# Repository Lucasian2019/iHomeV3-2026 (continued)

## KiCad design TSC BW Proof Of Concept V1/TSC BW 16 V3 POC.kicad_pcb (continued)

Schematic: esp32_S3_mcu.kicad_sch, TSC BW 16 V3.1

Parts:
C7: 0.1uF; C_1206_3216Metric
C8: 22uF; C_1206_3216Metric
J3: Free GPIO !pull-up; PhoenixContact_MSTBA_2,5_3-G-5,08_1x03_P5.08mm_Horizontal
J4: Free GPIO pull-up; PhoenixContact_MSTBA_2,5_3-G-5,08_1x03_P5.08mm_Horizontal
J19: 691312510002; PhoenixContact_MSTBA_2,5_2-G-5,08_1x02_P5.08mm_Horizontal
R5, R6: 4.7k; R_1206_3216Metric_Pad1.30x1.75mm_HandSolder
R7, R8, R9: 10k; R_1206_3216Metric_Pad1.30x1.75mm_HandSolder
U3: ESP32-S3-WROOM-1

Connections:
485RX: U3.10 (IO17); also elsewhere on the board
485TX: U3.9 (IO16); also elsewhere on the board
485_EN: U3.23 (IO21); also elsewhere on the board
+3V3: C7.2, C8.2, R5.1, R6.1, R7.2, R8.2, R9.2, U3.2 (3V3); also elsewhere on the board
/ESP32 S3 MCU/F_IO38: J4.1, R7.1, U3.31 (IO38)
/ESP32 S3 MCU/F_IO39: J3.1, U3.32 (IO39)
/ESP32 S3 MCU/F_IO40: J3.2, U3.33 (IO40)
/ESP32 S3 MCU/F_IO41: J3.3, U3.34 (IO41)
/ESP32 S3 MCU/F_IO47: J4.2, R8.1, U3.24 (IO47)
/ESP32 S3 MCU/F_IO48: J4.3, R9.1
ANALOG_A1: U3.4 (IO4); also elsewhere on the board
ANALOG_A2: U3.6 (IO6); also elsewhere on the board
ANALOG_A3: U3.7 (IO7); also elsewhere on the board
ANALOG_A4: U3.5 (IO5); also elsewhere on the board
BUZZER: U3.25 (IO48); also elsewhere on the board
EN: U3.3 (EN); also elsewhere on the board
ETH_INT: U3.38 (IO2); also elsewhere on the board
ETH_MISO: U3.14 (USB_D+); also elsewhere on the board
ETH_MOSI: U3.13 (USB_D-); also elsewhere on the board
ETH_RST: U3.39 (IO1); also elsewhere on the board
ETH_SCLK: U3.35 (IO42); also elsewhere on the board
ETH_SCS: U3.8 (IO15); also elsewhere on the board
GND: C7.1, C8.1, U3.1 (GND), U3.40 (GND), U3.41 (GND); also elsewhere on the board
IO0: U3.27 (IO0); also elsewhere on the board
RXD: U3.36 (RXD0); also elsewhere on the board
SCL: J19.1, R6.2, U3.18 (IO10); also elsewhere on the board
SDA: J19.2, R5.2, U3.17 (IO9); also elsewhere on the board
SD_CLK: U3.21 (IO13)
SD_CS: U3.19 (IO11); also elsewhere on the board
SD_MISO: U3.22 (IO14)
SD_MOSI: U3.20 (IO12); also elsewhere on the board
TXD: U3.37 (TXD0); also elsewhere on the board

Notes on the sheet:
free GPIOs with pull-up: f-io-1:GPIO39 f-io-2:GPIO40 f-io-3:GPIO41
BUZZER - PIN25 : GPIO48
Pull-Up Resistors
SD CARD GLOBAL PINS / LABELS P7
BUZZER GLOBAL PINS / LABELS P13
RS485 TXD - PIN9 : GPIO16 RXD - PIN10 : GPIO17 TXD - PIN23 : GPIO21
1 RTC P6
SDA - PIN17 : GPIO9 SCL - PIN18 : GPIO10
3 DIGITAL OUTPUT P5
Ethernet (W5500) ETH_SCLK - PIN35 : GPIO42 ETH_MOSI - PIN37 : GPIO43 ETH_MISO - PIN36 : GPIO44 ETH_SCS - PIN8 : GPIO15 ETH_INT - PIN38 : GPIO2 ETH_RST - PIN39 : GPIO1
USB C - UART EN- PIN3 : NO GPIO IO0 - PIN27 : GPIO0 RXD - PIN36/RXD0 : GPIO44,U0RXD TXD - PIN37/ TXD0 : GPIO43,U0TXD
i2c sda: 9 scl: 10
SD Card (SPI) MOSI - PIN20 : GPIO12 SCK - PIN21 : GPIO13 MISO - PIN22 : GPIO14 CS - PIN19 : GPIO11 SD-CD - PIN23 : GPIO21
2 DIGITAL INPUT P4
FREE GPIO with pull-up on PCB 1 - PIN31 : GPIO38 2 - PIN24 : GPIO47 3 - PIN25 : GPIO48
ETHERNET GLOBAL PINS / LABELS P15
Analog Inputs ANALOG_A1 - PIN4 : GPIO4 ANALOG_A2 - PIN6 : GPIO6 ANALOG_A3 - PIN7 : GPIO7 ANALOG_A4 - PIN5 : GPIO5
I2C PULL UPS
I2C GLOBAL PINS / LABELS
USB C - UART GLOBAL PINS / LABELS P11
ADC PINS / LABELS P14
RS485 V2 GLOBAL PINS / LABELS P10
free GPIOs without pull-up: f-io-1:GPIO39 f-io-2:GPIO40 f-io-3:GPIO41
Free GPIOs (without pull-up on PCB) 1 - PIN32 : GPIO39 2 - PIN33 : GPIO40 3 - PIN34 : GPIO41

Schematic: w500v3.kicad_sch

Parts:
C47, C48: 12pF; C_0603_1608Metric_Pad1.08x0.95mm_HandSolder
C49, C50, C51, C52, C53, C54, C64: 100nF; C_0603_1608Metric_Pad1.08x0.95mm_HandSolder
C55, C59: 10nF; C_0603_1608Metric_Pad1.08x0.95mm_HandSolder
C56: 4.7uF/6.3V; C_0603_1608Metric_Pad1.08x0.95mm_HandSolder
C57: 22nF; C_0603_1608Metric_Pad1.08x0.95mm_HandSolder
C61: 102/1KV; C_0603_1608Metric_Pad1.08x0.95mm_HandSolder
C62, C63: 10uF/10v; C_0603_1608Metric_Pad1.08x0.95mm_HandSolder
C65, C66: 6.8nF; C_0603_1608Metric_Pad1.08x0.95mm_HandSolder
J18: RJ45_Hanrun_HR911105A_Horizontal
JP5: SolderJumper_2_Open; SolderJumper-2_P1.3mm_Open_RoundedPad1.0x1.5mm
R183, R186: 10K; R_0603_1608Metric_Pad0.98x0.95mm_HandSolder
R184: 10K; R_0603_1608Metric
R188: 12.4k 1%; R_0603_1608Metric_Pad0.98x0.95mm_HandSolder
R189, R190: 49R9; R_0603_1608Metric_Pad0.98x0.95mm_HandSolder
R191: 10R; R_0603_1608Metric_Pad0.98x0.95mm_HandSolder
R192, R193: 82R; R_0603_1608Metric_Pad0.98x0.95mm_HandSolder
R194: 1M; R_0603_1608Metric_Pad0.98x0.95mm_HandSolder
R197, R198: 1k; R_0603_1608Metric_Pad0.98x0.95mm_HandSolder
RN3: R_Pack04; R_Array_Convex_4x0603
RN10: 10K R_Pack05; R_Array_Convex_5x0603
U46: W5500; LQFP-48_7x7mm_P0.5mm
Y4: 25M; Crystal_SMD_3225-4Pin_3.2x2.5mm

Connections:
+3V3: JP5.1 (A); also elsewhere on the board
+3V3 VW: C49.1, C50.1, C51.1, C52.2, C53.1, C54.1, C62.1, C63.1, C64.1, J18.9, J18.12, JP5.2 (B), R183.1, R184.1, R186.2, R189.1, R190.1, R191.2, RN3.1 (R1.1), RN3.2 (R2.1), RN3.3 (R3.1), U46.4 (AVDD), U46.8 (AVDD), U46.11 (AVDD), U46.15 (AVDD), U46.17 (AVDD), U46.21 (AVDD), U46.28 (VDD)
/W500 v3/ActLed: R198.1, U46.27 (ACTLED)
/W500 v3/LinkedLed: R197.1, U46.25 (LINKLED)
/W500 v3/RCT: C59.2, J18.5 (RCT), R192.1, R193.2
/W500 v3/RD+: C65.2, J18.3 (RD+)
/W500 v3/RD-: C66.2, J18.6 (RD-)
/W500 v3/RXN-: C66.1, R193.1, U46.5 (RXN)
/W500 v3/RXP+: C65.1, R192.2, U46.6 (RXP)
/W500 v3/TCT: C57.1, J18.4 (TCT), R191.1
/W500 v3/TD+: J18.1 (TD+), R190.2, U46.2 (TXP)
/W500 v3/TD-: J18.2 (TD-), R189.2, U46.1 (TXN)
/W500 v3/X0: C48.2, U46.31 (XO), Y4.2
/W500 v3/X1: C47.2, U46.30 (XI/CLKIN), Y4.1
CGND: C61.2, J18.SH, R194.1
ETH_INT: R184.2, U46.36 (~INT); also elsewhere on the board
ETH_MISO: U46.34 (MISO); also elsewhere on the board
ETH_MOSI: U46.35 (MOSI); also elsewhere on the board
ETH_RST: R183.2, U46.37 (~RST); also elsewhere on the board
ETH_SCLK: U46.33 (SCLK); also elsewhere on the board
ETH_SCS: R186.1, U46.32 (~SCS); also elsewhere on the board
GND: C47.1, C48.1, C49.2, C50.2, C51.2, C52.1, C53.2, C54.2, C55.1, C56.2, C57.2, C59.1, C61.1, C62.2, C63.2, C64.2, J18.8, R188.2, R194.2, RN3.4 (R4.1), RN10.6 (R5.2), RN10.7 (R4.2), RN10.8 (R3.2), RN10.9 (R2.2), RN10.10 (R1.2), U46.3 (AGND), U46.9 (AGND), U46.14 (AGND), U46.16 (AGND), U46.19 (AGND), U46.29 (GND), U46.48 (AGND); also elsewhere on the board
unnamed: J18.10, R198.2
unnamed: J18.11, R197.2
unnamed: RN3.8 (R1.2), U46.45 (PMODE0)
unnamed: RN3.7 (R2.2), U46.44 (PMODE1)
unnamed: RN3.6 (R3.2), U46.43 (PMODE2)
unnamed: RN3.5 (R4.2), U46.38 (RSVD)
unnamed: RN10.1 (R1.1), U46.23 (RSVD)
unnamed: RN10.2 (R2.1), U46.42 (RSVD)
unnamed: RN10.3 (R3.1), U46.41 (RSVD)
unnamed: RN10.4 (R4.1), U46.40 (RSVD)
unnamed: RN10.5 (R5.1), U46.39 (RSVD)
unnamed: C55.2, U46.22 (1V2O)
unnamed: R188.1, U46.10 (EXRES1)
unnamed: C56.1, U46.20 (TOCAP)

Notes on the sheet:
ethernet: type: W5500 clk_pin: GPIO42 mosi_pin: GPIO43 miso_pin: GPIO44 cs_pin: GPIO15 interrupt_pin: GPIO2 reset_pin: GPIO1
GLOBAL PINS / LABELS

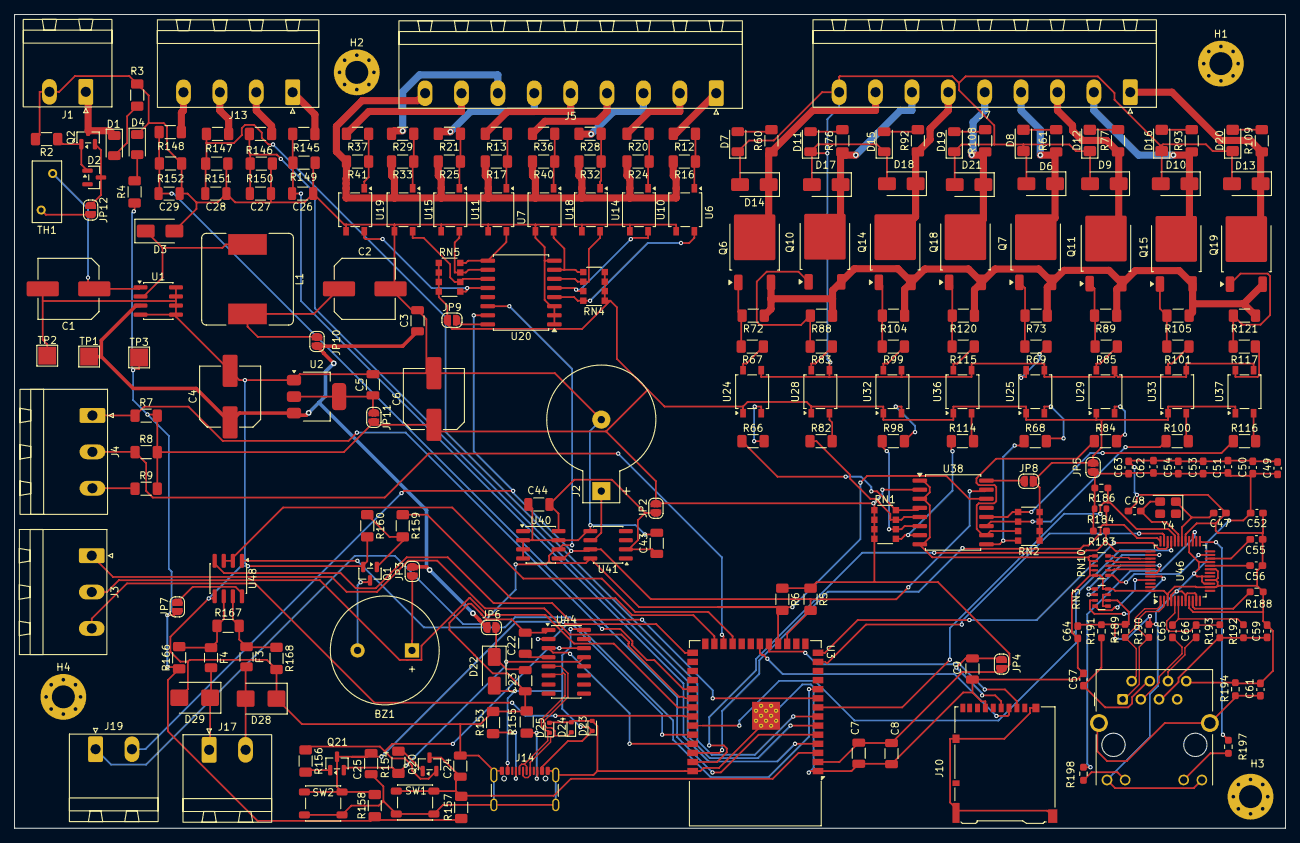
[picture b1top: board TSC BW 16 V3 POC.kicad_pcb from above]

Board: 2 copper layers, 177.4 x 113.6 mm, 232 parts (0 on the bottom side), 172 nets.

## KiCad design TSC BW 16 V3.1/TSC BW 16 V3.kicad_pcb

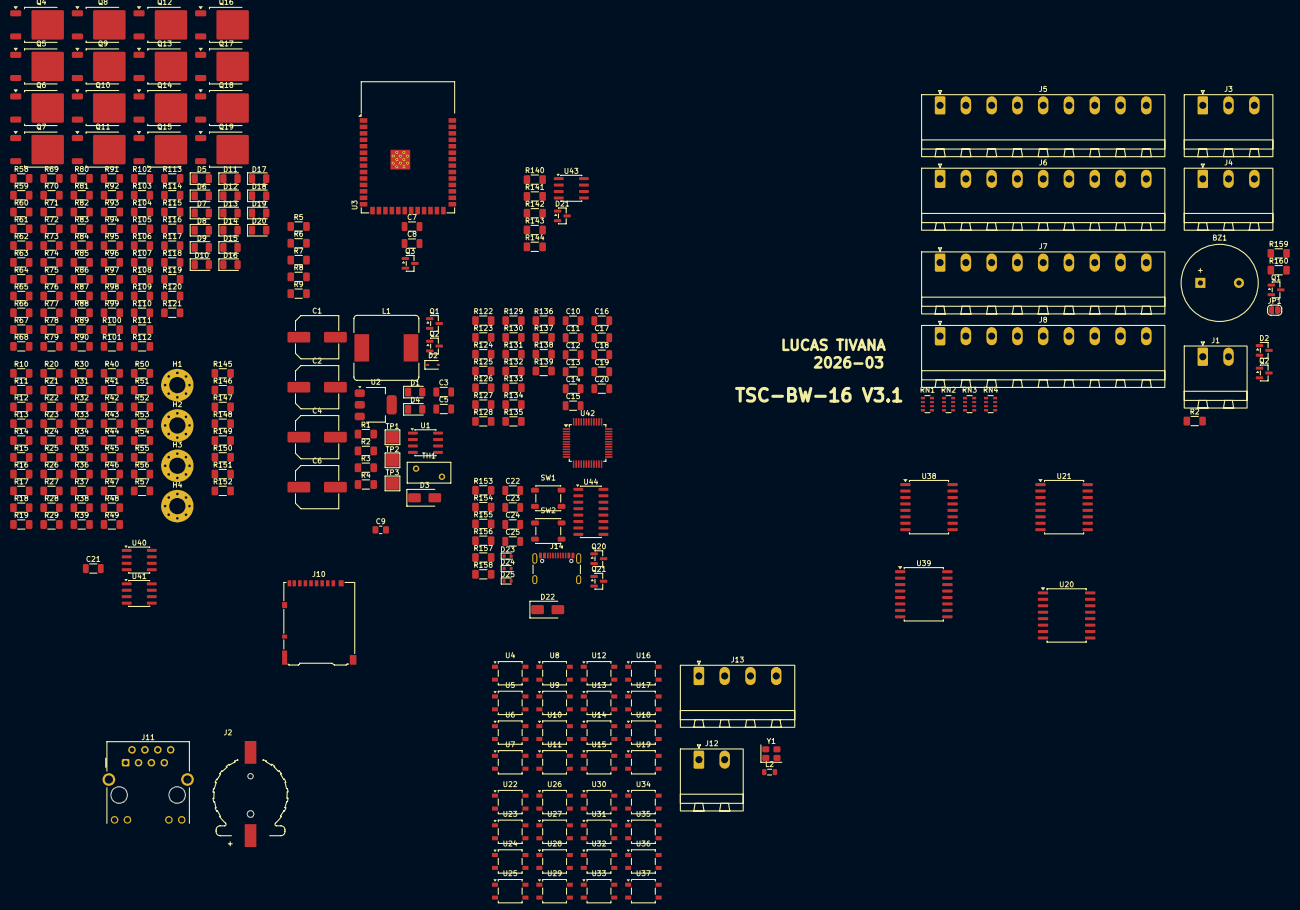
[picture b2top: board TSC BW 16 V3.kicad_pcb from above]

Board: 2 copper layers, 311 parts (0 on the bottom side), 232 nets, no tracks yet.

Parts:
BZ1: Buzzer; Buzzer_15x7.5RM7.6
C1: 100uF/35V; C_Elec_8x10.2
C2, C6: 220uF/10V; C_Elec_8x10.2
C3, C5, C23, C24, C25: 100nF; C_1206_3216Metric
C4: 47uF/25V; C_Elec_8x10.2
C7, C10, C21: 0.1uF; C_1206_3216Metric
C8: 22uF; C_1206_3216Metric
C9: 22uF; C_0805_2012Metric_Pad1.18x1.45mm_HandSolder
C11: 1uF; C_1206_3216Metric
C12: 10uF; C_1206_3216Metric
C13, C16: 22nF; C_1206_3216Metric
C14, C15: 6.8nF; C_1206_3216Metric
C17: 4.7uF; C_1206_3216Metric
C18, C19: 18pF; C_1206_3216Metric
C20, C22: 10nF; C_1206_3216Metric
D1, D4, D5, D6, D7, D8, D9, D10, D11, D12, D13, D14, D15, D16, D17, D18, D19, D20: IR26-21C_L110_TR8; LED_1206_3216Metric
D2: BZX84C15; SOT-23
D2#2: 1N4148WS; D_SOD-323
D3, D22: SS36; D_SMA
D21: SM712_SOT23; SOT-23
D23, D24, D25: LESD5D5.0CT1G; D_SOD-523
H1, H2, H3, H4: MountingHole_Pad; MountingHole_3.2mm_M3_Pad_Via
J1, J12: 691312510002; PhoenixContact_MSTBA_2,5_2-G-5,08_1x02_P5.08mm_Horizontal
J2: CR1220_S8411_45R; CR1220_HARWIN_S8411-45R
J3: Free GPIO !pull-up; PhoenixContact_MSTBA_2,5_3-G-5,08_1x03_P5.08mm_Horizontal
J4: Free GPIO pull-up; PhoenixContact_MSTBA_2,5_3-G-5,08_1x03_P5.08mm_Horizontal
J5, J6, J7, J8: Terminal Plug; PhoenixContact_MSTBA_2,5_9-G-5,08_1x09_P5.08mm_Horizontal
J10: Micro_SD_Card_Det_Hirose_DM3AT; microSD_HC_Hirose_DM3AT-SF-PEJM5
J11: RJ45_Hanrun_HR911105A_Horizontal; RJ45_Hanrun_HR911105A_Horizontal_3D
J13: Analog Inputs; PhoenixContact_MSTBA_2,5_4-G-5,08_1x04_P5.08mm_Horizontal
J14: USB_C_Receptacle_USB2.0_16P; USB_C_Receptacle_GCT_USB4105-xx-A_16P_TopMnt_Horizontal
JP1: SolderJumper_2_Open; SolderJumper-2_P1.3mm_Open_RoundedPad1.0x1.5mm
L1: 68uH/2A; L_Bourns_SRR1260
L2: 120ohm; L_0805_2012Metric
Q1: BC817; SOT-23
Q1#2: IRLML6402; SOT-23
Q2: MMBT2222A; SOT-23
Q2#2: AO3401A; SOT-23
Q3: MMBTA06; SOT-23
Q4, Q5, Q6, Q7, Q8, Q9, Q10, Q11, Q12, Q13, Q14, Q15, Q16, Q17, Q18, Q19: NCE60P10K; TO-252-2
Q20, Q21: SS8050; SOT-23
R1, R2, R2#2: 10K; R_1206_3216Metric_Pad1.30x1.75mm_HandSolder
R3: 4K7; R_1206_3216Metric_Pad1.30x1.75mm_HandSolder
R4: 1k/1%; R_1206_3216Metric_Pad1.30x1.75mm_HandSolder
R5, R6, R42, R43, R44, R45, R46, R47, R48, R49, R50, R51, R52, R53, R54, R55, R56, R57: 4.7k; R_1206_3216Metric_Pad1.30x1.75mm_HandSolder
R7, R8, R9, R14, R15, R16, R17, R22, R23, R24, R25, R30, R31, R32, R33, R38, R39, R40, R41, R127, R129, R132, R133, R134, R154, R156, R157, R158: 10k; R_1206_3216Metric_Pad1.30x1.75mm_HandSolder
R10, R11, R12, R13, R18, R19, R20, R21, R26, R27, R28, R29, R34, R35, R36, R37, R62, R64, R66, R68, R78, R80, R82, R84, R94, R96, R98, R100, R110, R112, R114, R116, R159: 1k; R_1206_3216Metric_Pad1.30x1.75mm_HandSolder
R58, R59, R60, R61, R74, R75, R76, R77, R90, R91, R92, R93, R106, R107, R108, R109: 4.7K; R_1206_3216Metric_Pad1.30x1.75mm_HandSolder
R63, R65, R67, R69, R79, R81, R83, R85, R95, R97, R99, R101, R111, R113, R115, R117: 8.2k; R_1206_3216Metric_Pad1.30x1.75mm_HandSolder
R70, R71, R72, R73, R86, R87, R88, R89, R102, R103, R104, R105, R118, R119, R120, R121: 5.1K; R_1206_3216Metric_Pad1.30x1.75mm_HandSolder
R122, R123, R136, R137: 50R; R_1206_3216Metric_Pad1.30x1.75mm_HandSolder
R124: 10R 1%; R_1206_3216Metric_Pad1.30x1.75mm_HandSolder
R125, R126, R128, R130: 33R; R_1206_3216Metric_Pad1.30x1.75mm_HandSolder
R131, R135: 330R; R_1206_3216Metric_Pad1.30x1.75mm_HandSolder
R138: 1M; R_1206_3216Metric_Pad1.30x1.75mm_HandSolder
R139: 12.4k 1%; R_1206_3216Metric_Pad1.30x1.75mm_HandSolder
R140, R144: 680E; R_1206_3216Metric_Pad1.30x1.75mm_HandSolder
R141, R143: 10E; R_1206_3216Metric_Pad1.30x1.75mm_HandSolder
R142: 120E; R_1206_3216Metric_Pad1.30x1.75mm_HandSolder
R145, R146, R147, R148, R149, R150, R151, R152: *; R_1206_3216Metric_Pad1.30x1.75mm_HandSolder
R153, R155: 5.1k; R_1206_3216Metric_Pad1.30x1.75mm_HandSolder
R160: 100k; R_1206_3216Metric_Pad1.30x1.75mm_HandSolder
RN1, RN2, RN3, RN4: resister_array_4_10k_CAY16-103J4LF; R_Array_Convex_4x0603
SW1, SW2: SW_Push; SW_SPST_PTS647_Sx38
TH1: NTC 10D-7; Fuse_BelFuse_0ZRE0012FF_L8.3mm_W3.8mm
TP1, TP2, TP3: TestPoint; TestPoint_Pad_2.5x2.5mm
U1: XL1509-5.0; SOIC-8_3.9x4.9mm_P1.27mm
U2: AMS1117-3.3; SOT-223-3_TabPin2
U3: ESP32-S3-WROOM-1
U4, U5, U6, U7, U8, U9, U10, U11, U12, U13, U14, U15, U16, U17, U18, U19, U22, U23, U24, U25, U26, U27, U28, U29, U30, U31, U32, U33, U34, U35, U36, U37: PC357C; SO-4_4.4x4.3mm_P2.54mm
U20, U21, U38, U39: PCF8574T; SOIC-16W_7.5x10.3mm_P1.27mm
U40: AT24CS04-SSHM; SOIC-8_3.9x4.9mm_P1.27mm
U41: DS3231MZ; SOIC-8_3.9x4.9mm_P1.27mm
U42: W5500; LQFP-48_7x7mm_P0.5mm
U43: SN65HVD75; SOIC-8_3.9x4.9mm_P1.27mm
U44: CH340C; SOIC-16_3.9x9.9mm_P1.27mm
Y1: C2E-25.000-10-3030-X-R; Crystal_SMD_3225-4Pin_3.2x2.5mm

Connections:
+3V3: C5.1, C6.1, C7.2, C8.2, C9.1, C21.2, J10.4 (VDD), L2.2, R4.1, R5.1, R6.1, R7.2, R8.2, R9.2, R42.1, R43.1, R44.1, R45.1, R46.1, R47.1, R48.1, R49.1, R50.1, R51.1, R52.1, R53.1, R54.1, R55.1, R56.1, R57.1, R62.1, R64.1, R66.1, R68.1, R78.1, R80.1, R82.1, R84.1, R94.1, R96.1, R98.1, R100.1, R110.1, R112.1, R114.1, R116.1, R131.2, R135.2, R140.1, R157.1, R158.1, RN1.1, RN1.2, RN1.3, RN1.4, RN2.1, RN2.2, RN2.3, RN2.4, RN3.1, RN3.2, RN3.3, RN3.4, RN4.1, RN4.2, RN4.3, RN4.4, TP3.1 (1_1), U2.2 (VO), U3.2 (3V3), U20.16 (VDD), U21.1 (A0), U21.16 (VDD), U38.2 (A1), U38.16 (VDD), U39.1 (A0), U39.2 (A1), U39.16 (VDD), U40.8 (VCC), U41.2 (VCC), U43.8 (VCC)
+3V3 VA: C10.1, C11.1, C12.1, L2.1, R122.1, R123.1, R124.1, R127.1, R129.1, R132.1, R133.1, R134.1, U42.28 (VDD)
+5V: BZ1.1 (+), C2.1, C3.1, C4.1, C23.1, D22.1 (K), L1.2, TP1.1 (1_1), U1.3 (FB), U2.3 (VI)
+12V: D1.1 (K), J1.1, Q1#2.3 (D), Q2#2.3 (D), R1.1
/16 DIGITAL INPUTS/IN_P0: R42.2, U6.4, U20.4 (P0)
/16 DIGITAL INPUTS/IN_P1: R44.2, U10.4, U20.5 (P1)
/16 DIGITAL INPUTS/IN_P2: R46.2, U14.4, U20.6 (P2)
/16 DIGITAL INPUTS/IN_P3: R48.2, U18.4, U20.7 (P3)
/16 DIGITAL INPUTS/IN_P4: R50.2, U7.4, U20.9 (P4)
/16 DIGITAL INPUTS/IN_P5: R52.2, U11.4, U20.10 (P5)
/16 DIGITAL INPUTS/IN_P6: R54.2, U15.4, U20.11 (P6)
/16 DIGITAL INPUTS/IN_P7: R56.2, U19.4, U20.12 (P7)
/16 DIGITAL INPUTS/IN_P8: R43.2, U4.4, U21.4 (P0)
/16 DIGITAL INPUTS/IN_P9: R45.2, U8.4, U21.5 (P1)
/16 DIGITAL INPUTS/IN_P10: R47.2, U12.4, U21.6 (P2)
/16 DIGITAL INPUTS/IN_P11: R49.2, U16.4, U21.7 (P3)
/16 DIGITAL INPUTS/IN_P12: R51.2, U5.4, U21.9 (P4)
/16 DIGITAL INPUTS/IN_P13: R53.2, U9.4, U21.10 (P5)
/16 DIGITAL INPUTS/IN_P14: R55.2, U13.4, U21.11 (P6)
/16 DIGITAL INPUTS/IN_P15: R57.2, U17.4, U21.12 (P7)
/16 DIGITAL INPUTS/Input1: J5.1, R12.2
/16 DIGITAL INPUTS/Input2: J5.2, R20.2
/16 DIGITAL INPUTS/Input3: J5.3, R28.2
/16 DIGITAL INPUTS/Input4: J5.4, R36.2
/16 DIGITAL INPUTS/Input5: J5.5, R13.2
/16 DIGITAL INPUTS/Input6: J5.6, R21.2
/16 DIGITAL INPUTS/Input7: J5.7, R29.2
/16 DIGITAL INPUTS/Input8: J5.8, R37.2
/16 DIGITAL INPUTS/Input9: J6.1, R10.2
/16 DIGITAL INPUTS/Input10: J6.2, R18.2
/16 DIGITAL INPUTS/Input11: J6.3, R26.2
/16 DIGITAL INPUTS/Input12: J6.4, R34.2
/16 DIGITAL INPUTS/Input13: J6.5, R11.2
/16 DIGITAL INPUTS/Input14: J6.6, R19.2
/16 DIGITAL INPUTS/Input15: J6.7, R27.2
/16 DIGITAL INPUTS/Input16: J6.8, R35.2
/16 DIGITAL INPUTS/SCL: U20.14 (SCL), U21.14 (SCL)
/16 DIGITAL INPUTS/SDA: U20.15 (SDA), U21.15 (SDA)
/16 DIGITAL OUTPUTS/OT0: RN1.8, U24.2, U38.4 (P0)
/16 DIGITAL OUTPUTS/OT1: RN1.7, U28.2, U38.5 (P1)
/16 DIGITAL OUTPUTS/OT2: RN1.6, U32.2, U38.6 (P2)
/16 DIGITAL OUTPUTS/OT3: RN1.5, U36.2, U38.7 (P3)
/16 DIGITAL OUTPUTS/OT4: RN2.8, U25.2, U38.9 (P4)
/16 DIGITAL OUTPUTS/OT5: RN2.7, U29.2, U38.10 (P5)
/16 DIGITAL OUTPUTS/OT6: RN2.6, U33.2, U38.11 (P6)
/16 DIGITAL OUTPUTS/OT7: RN2.5, U37.2, U38.12 (P7)
/16 DIGITAL OUTPUTS/OT8: RN3.8, U22.2, U39.4 (P0)
/16 DIGITAL OUTPUTS/OT9: RN3.7, U26.2, U39.5 (P1)
/16 DIGITAL OUTPUTS/OT10: RN3.6, U30.2, U39.6 (P2)
/16 DIGITAL OUTPUTS/OT11: RN3.5, U34.2, U39.7 (P3)
/16 DIGITAL OUTPUTS/OT12: RN4.8, U23.2, U39.9 (P4)
/16 DIGITAL OUTPUTS/OT13: RN4.7, U27.2, U39.10 (P5)
/16 DIGITAL OUTPUTS/OT14: RN4.6, U31.2, U39.11 (P6)
/16 DIGITAL OUTPUTS/OT15: RN4.5, U35.2, U39.12 (P7)
/16 DIGITAL OUTPUTS/SCL: U38.14 (SCL), U39.14 (SCL)
/16 DIGITAL OUTPUTS/SDA: U38.15 (SDA), U39.15 (SDA)
/16 DIGITAL OUTPUTS/outp1: J7.8, Q6.2 (D), R60.1
/16 DIGITAL OUTPUTS/outp2: J7.7, Q10.2 (D), R76.1
/16 DIGITAL OUTPUTS/outp3: J7.6, Q14.2 (D), R92.1
/16 DIGITAL OUTPUTS/outp4: J7.5, Q18.2 (D), R108.1
/16 DIGITAL OUTPUTS/outp5: J7.4, Q7.2 (D), R61.1
/16 DIGITAL OUTPUTS/outp6: J7.3, Q11.2 (D), R77.1
/16 DIGITAL OUTPUTS/outp7: J7.2, Q15.2 (D), R93.1
/16 DIGITAL OUTPUTS/outp8: J7.1, Q19.2 (D), R109.1
/16 DIGITAL OUTPUTS/outp9: J8.8, Q4.2 (D), R58.1
/16 DIGITAL OUTPUTS/outp10: J8.7, Q8.2 (D), R74.1
/16 DIGITAL OUTPUTS/outp11: J8.6, Q12.2 (D), R90.1
/16 DIGITAL OUTPUTS/outp12: J8.5, Q16.2 (D), R106.1
/16 DIGITAL OUTPUTS/outp13: J8.4, Q5.2 (D), R59.1
/16 DIGITAL OUTPUTS/outp14: J8.3, Q9.2 (D), R75.1
/16 DIGITAL OUTPUTS/outp15: J8.2, Q13.2 (D), R91.1
/16 DIGITAL OUTPUTS/outp16: J8.1, Q17.2 (D), R107.1
/ADC PINS/ANALOG_A1: R145.2, R149.1
/ADC PINS/ANALOG_A1_INPUT: J13.1, R145.1
/ADC PINS/ANALOG_A2: R146.2, R150.1
/ADC PINS/ANALOG_A2_INPUT: J13.2, R146.1
/ADC PINS/ANALOG_A3: R147.2, R151.1
/ADC PINS/ANALOG_A3_INPUT: J13.3, R147.1
/ADC PINS/ANALOG_A4: R148.2, R152.1
/ADC PINS/ANALOG_A4_INPUT: J13.4, R148.1
/ESP32 S3 MCU/F_IO38: J4.1, R7.1, U3.31 (IO38)
/ESP32 S3 MCU/F_IO39: J3.1, U3.32 (IO39)
/ESP32 S3 MCU/F_IO40: J3.2, U3.33 (IO40)
/ESP32 S3 MCU/F_IO41: J3.3, U3.34 (IO41)
/ESP32 S3 MCU/F_IO47: J4.2, R8.1, U3.24 (IO47)
/ESP32 S3 MCU/F_IO48: J4.3, R9.1, U3.25 (IO48)
/ESP32 S3 MCU/SCL: R6.2, U3.18 (IO10)
/ESP32 S3 MCU/SDA: R5.2, U3.17 (IO9)
/ETHERNET/1RD+: C15.1, R130.2, R136.2
/ETHERNET/1RD-: C14.1, R128.2, R137.2
/ETHERNET/ActLed: J11.10, U42.27 (ACTLED)
/ETHERNET/INT: R127.2, U42.36 (~INT)
/ETHERNET/LinkedLed: J11.11, U42.25 (LINKLED)
/ETHERNET/RCT: C16.1, J11.5 (RCT), R136.1, R137.1
/ETHERNET/RD+: C15.2, J11.3 (RD+)
/ETHERNET/RD-: C14.2, J11.6 (RD-)
/ETHERNET/RST: R129.2, U42.37 (~RST)
/ETHERNET/RXN: R128.1, U42.5 (RXN)
/ETHERNET/RXP: R130.1, U42.6 (RXP)
/ETHERNET/TCT: C13.1, J11.4 (TCT), R124.2
/ETHERNET/TD+: J11.1 (TD+), R123.2, R126.2
/ETHERNET/TD-: J11.2 (TD-), R122.2, R125.2
/ETHERNET/TXN: R125.1, U42.1 (TXN)
/ETHERNET/TXP: R126.1, U42.2 (TXP)
/ETHERNET/X0: C18.2, R138.1, U42.31 (XO), Y1.1
/ETHERNET/X1: C19.2, R138.2, U42.30 (XI/CLKIN), Y1.3
/Power Supply/Vprotected: D2.3 (K), Q1#2.2 (S), Q2#2.2 (S), R2#2.1, TH1.1
/RS485/RS485+: D21.2 (A2), J12.2, R142.2, R143.2, R144.2
/RS485/RS485-: D21.1 (A1), J12.1, R140.2, R141.2, R142.1
/RTC/SCL: U40.6 (SCL), U41.7 (SDA)
/RTC/SDA: U40.5 (SDA), U41.8 (SCL)
/USB_C to UART/D+: D24.1, J14.A6 (D+), J14.B6 (D+), U44.5 (UD+)
/USB_C to UART/D-: D25.1, J14.A7 (D-), J14.B7 (D-), U44.6 (UD-)
/USB_C to UART/DTR: Q21.2 (E), R154.1, U44.13 (~DTR)
/USB_C to UART/RST: Q20.2 (E), R156.1, U44.14 (~RTS)
EN: C24.1, Q20.3 (C), R157.2, SW1.1, U3.3 (EN)
GND: C1.2, C2.2, C3.2, C4.2, C5.2, C6.2, C7.1, C8.1, C9.2, C10.2, C11.2, C12.2, C13.2, C16.2, C17.2, C18.1, C19.1, C20.2, C21.1, C22.1, C23.2, C24.2, C25.2, D2#2.2 (A), D3.2 (A), D4.1 (K), D21.3 (common), D23.2, D24.2, D25.2, J1.2, J2.N, J10.6 (VSS), J11.8, J14.A1 (GND), J14.A12 (GND), J14.B1 (GND), J14.B12 (GND), J14.S1 (SHIELD), Q1.2 (E), Q2.2 (E), Q3.2 (E), R2.2, R3.2, R139.2, R144.1, R149.2, R150.2, R151.2, R152.2, R153.2, R155.2, R160.2, SW1.2, SW2.2, TP2.1 (1_1), U1.4 (~EN), U1.5 (GND), U1.6 (GND), U1.7 (GND), U1.8 (GND), U2.1 (GND), U3.1 (GND), U3.40 (GND), U3.41 (GND), U4.3, U5.3, U6.3, U7.3, U8.3, U9.3, U10.3, U11.3, U12.3, U13.3, U14.3, U15.3, U16.3, U17.3, U18.3, U19.3, U20.1 (A0), U20.2 (A1), U20.3 (A2), U20.8 (GND), U21.2 (A1), U21.3 (A2), U21.8 (GND), U38.1 (A0), U38.3 (A2), U38.8 (GND), U39.3 (A2), U39.8 (GND), U40.2 (A1), U40.3 (A2), U40.4 (GND), U40.7 (WP), U41.5 (GND), U42.29 (GND), U43.5 (GND), Y1.2 (GND), Y1.4 (GND)
IO0: C25.1, Q21.3 (C), R158.2, SW2.1, U3.27 (IO0)
MCU_EN_RS485: U43.2 (~RE), U43.3 (DE)
unnamed: BZ1.2 (-), Q1.3 (C), Q3.3 (C)
unnamed: D1.2 (A), R3.1
unnamed: D2.1 (A), Q2#2.1 (G), R2.1
unnamed: D2#2.1 (K), Q2.1 (B), R2#2.2
unnamed: D3.1 (K), L1.1, U1.2 (OUT)
unnamed: D4.2 (A), R4.2
unnamed: D5.2 (A), R58.2
unnamed: D6.2 (A), R59.2
unnamed: D7.2 (A), R60.2
unnamed: D8.2 (A), R61.2
unnamed: D9.2 (A), R74.2
unnamed: D10.2 (A), R75.2
unnamed: D11.2 (A), R76.2
unnamed: D12.2 (A), R77.2
unnamed: D13.2 (A), R90.2
unnamed: D14.2 (A), R91.2
unnamed: D15.2 (A), R92.2
unnamed: D16.2 (A), R93.2
unnamed: D17.2 (A), R106.2
unnamed: D18.2 (A), R107.2
unnamed: D19.2 (A), R108.2
unnamed: D20.2 (A), R109.2
unnamed: J11.9, R135.1
unnamed: J11.12, R131.1
unnamed: J14.A5 (CC1), R153.1
unnamed: J14.B5 (CC2), R155.1
unnamed: JP1.2 (B), R159.1
unnamed: Q1.1 (B), R159.2, R160.1
unnamed: Q1#2.1 (G), Q2.3 (C), R1.2
unnamed: Q4.1 (G), R63.2, R70.2
unnamed: Q5.1 (G), R65.2, R71.2
unnamed: Q6.1 (G), R67.2, R72.2
unnamed: Q7.1 (G), R69.2, R73.2
unnamed: Q8.1 (G), R79.2, R86.2
unnamed: Q9.1 (G), R81.2, R87.2
unnamed: Q10.1 (G), R83.2, R88.2
unnamed: Q11.1 (G), R85.2, R89.2
unnamed: Q12.1 (G), R95.2, R102.2
unnamed: Q13.1 (G), R97.2, R103.2
unnamed: Q14.1 (G), R99.2, R104.2
unnamed: Q15.1 (G), R101.2, R105.2
unnamed: Q16.1 (G), R111.2, R118.2
unnamed: Q17.1 (G), R113.2, R119.2
unnamed: Q18.1 (G), R115.2, R120.2
unnamed: Q19.1 (G), R117.2, R121.2
unnamed: Q20.1 (B), R154.2
unnamed: Q21.1 (B), R156.2
unnamed: R10.1, R14.1, U4.1
unnamed: R11.1, R15.1, U5.1
unnamed: R12.1, R16.1, U6.1
unnamed: R13.1, R17.1, U7.1
unnamed: R18.1, R22.1, U8.1
unnamed: R19.1, R23.1, U9.1
unnamed: R20.1, R24.1, U10.1
unnamed: R21.1, R25.1, U11.1
unnamed: R26.1, R30.1, U12.1
unnamed: R27.1, R31.1, U13.1
unnamed: R28.1, R32.1, U14.1
unnamed: R29.1, R33.1, U15.1
unnamed: R34.1, R38.1, U16.1
unnamed: R35.1, R39.1, U17.1
unnamed: R36.1, R40.1, U18.1
unnamed: R37.1, R41.1, U19.1
unnamed: R62.2, U22.1
unnamed: R63.1, U22.4
unnamed: R64.2, U23.1
unnamed: R65.1, U23.4
unnamed: R66.2, U24.1
unnamed: R67.1, U24.4
unnamed: R68.2, U25.1
unnamed: R69.1, U25.4
unnamed: R78.2, U26.1
unnamed: R79.1, U26.4
unnamed: R80.2, U27.1
unnamed: R81.1, U27.4
unnamed: R82.2, U28.1
unnamed: R83.1, U28.4
unnamed: R84.2, U29.1
unnamed: R85.1, U29.4
unnamed: R94.2, U30.1
unnamed: R95.1, U30.4
unnamed: R96.2, U31.1
unnamed: R97.1, U31.4
unnamed: R98.2, U32.1
unnamed: R99.1, U32.4
unnamed: R100.2, U33.1
unnamed: R101.1, U33.4
unnamed: R110.2, U34.1
unnamed: R111.1, U34.4
unnamed: R112.2, U35.1
unnamed: R113.1, U35.4
unnamed: R114.2, U36.1
unnamed: R115.1, U36.4
unnamed: R116.2, U37.1
unnamed: R117.1, U37.4
unnamed: C1.1, TH1.2, U1.1 (VIN)
unnamed: J2.P, U41.6 (VBAT)
unnamed: C20.1, U42.22 (1V2O)
unnamed: U42.3 (AGND), U42.9 (AGND), U42.14 (AGND), U42.16 (AGND), U42.19 (AGND), U42.48 (AGND)
unnamed: U42.4 (AVDD), U42.8 (AVDD), U42.11 (AVDD), U42.15 (AVDD), U42.17 (AVDD), U42.21 (AVDD)
unnamed: R139.1, U42.10 (EXRES1)
unnamed: R132.2, U42.45 (PMODE0)
unnamed: R133.2, U42.44 (PMODE1)
unnamed: R134.2, U42.43 (PMODE2)
unnamed: C17.1, U42.20 (TOCAP)
unnamed: R143.1, U43.6 (A)
unnamed: R141.1, U43.7 (B)
unnamed: C22.2, U44.4 (V3)
PGND: D5.1 (K), D6.1 (K), D7.1 (K), D8.1 (K), D9.1 (K), D10.1 (K), D11.1 (K), D12.1 (K), D13.1 (K), D14.1 (K), D15.1 (K), D16.1 (K), D17.1 (K), D18.1 (K), D19.1 (K), D20.1 (K), J5.9, J6.9, J7.9, J8.9, R14.2, R15.2, R16.2, R17.2, R22.2, R23.2, R24.2, R25.2, R30.2, R31.2, R32.2, R33.2, R38.2, R39.2, R40.2, R41.2, U4.2, U5.2, U6.2, U7.2, U8.2, U9.2, U10.2, U11.2, U12.2, U13.2, U14.2, U15.2, U16.2, U17.2, U18.2, U19.2, U22.3, U23.3, U24.3, U25.3, U26.3, U27.3, U28.3, U29.3, U30.3, U31.3, U32.3, U33.3, U34.3, U35.3, U36.3, U37.3
RXD: U3.36 (RXD0), U44.2 (TXD)
TXD: U3.37 (TXD0), U44.3 (RXD)
VBUS: D22.2 (A), D23.1, J14.A4 (VBUS), J14.A9 (VBUS), J14.B4 (VBUS), J14.B9 (VBUS), U44.16 (VCC)
VinLoad1: Q4.3 (S), Q5.3 (S), Q6.3 (S), Q7.3 (S), Q8.3 (S), Q9.3 (S), Q10.3 (S), Q11.3 (S), Q12.3 (S), Q13.3 (S), Q14.3 (S), Q15.3 (S), Q16.3 (S), Q17.3 (S), Q18.3 (S), Q19.3 (S), R70.1, R71.1, R72.1, R73.1, R86.1, R87.1, R88.1, R89.1, R102.1, R103.1, R104.1, R105.1, R118.1, R119.1, R120.1, R121.1

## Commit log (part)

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2026-06-18 Add KiCad gitignore
2026-06-18 Clean tracked files using gitignore
2026-06-18 Added kicad git cmd cheat sheet
